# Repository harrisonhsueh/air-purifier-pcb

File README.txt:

using tnis plugin to generate bom for jlpcb assembly
https://github.com/Bouni/kicad-jlcpcb-tools

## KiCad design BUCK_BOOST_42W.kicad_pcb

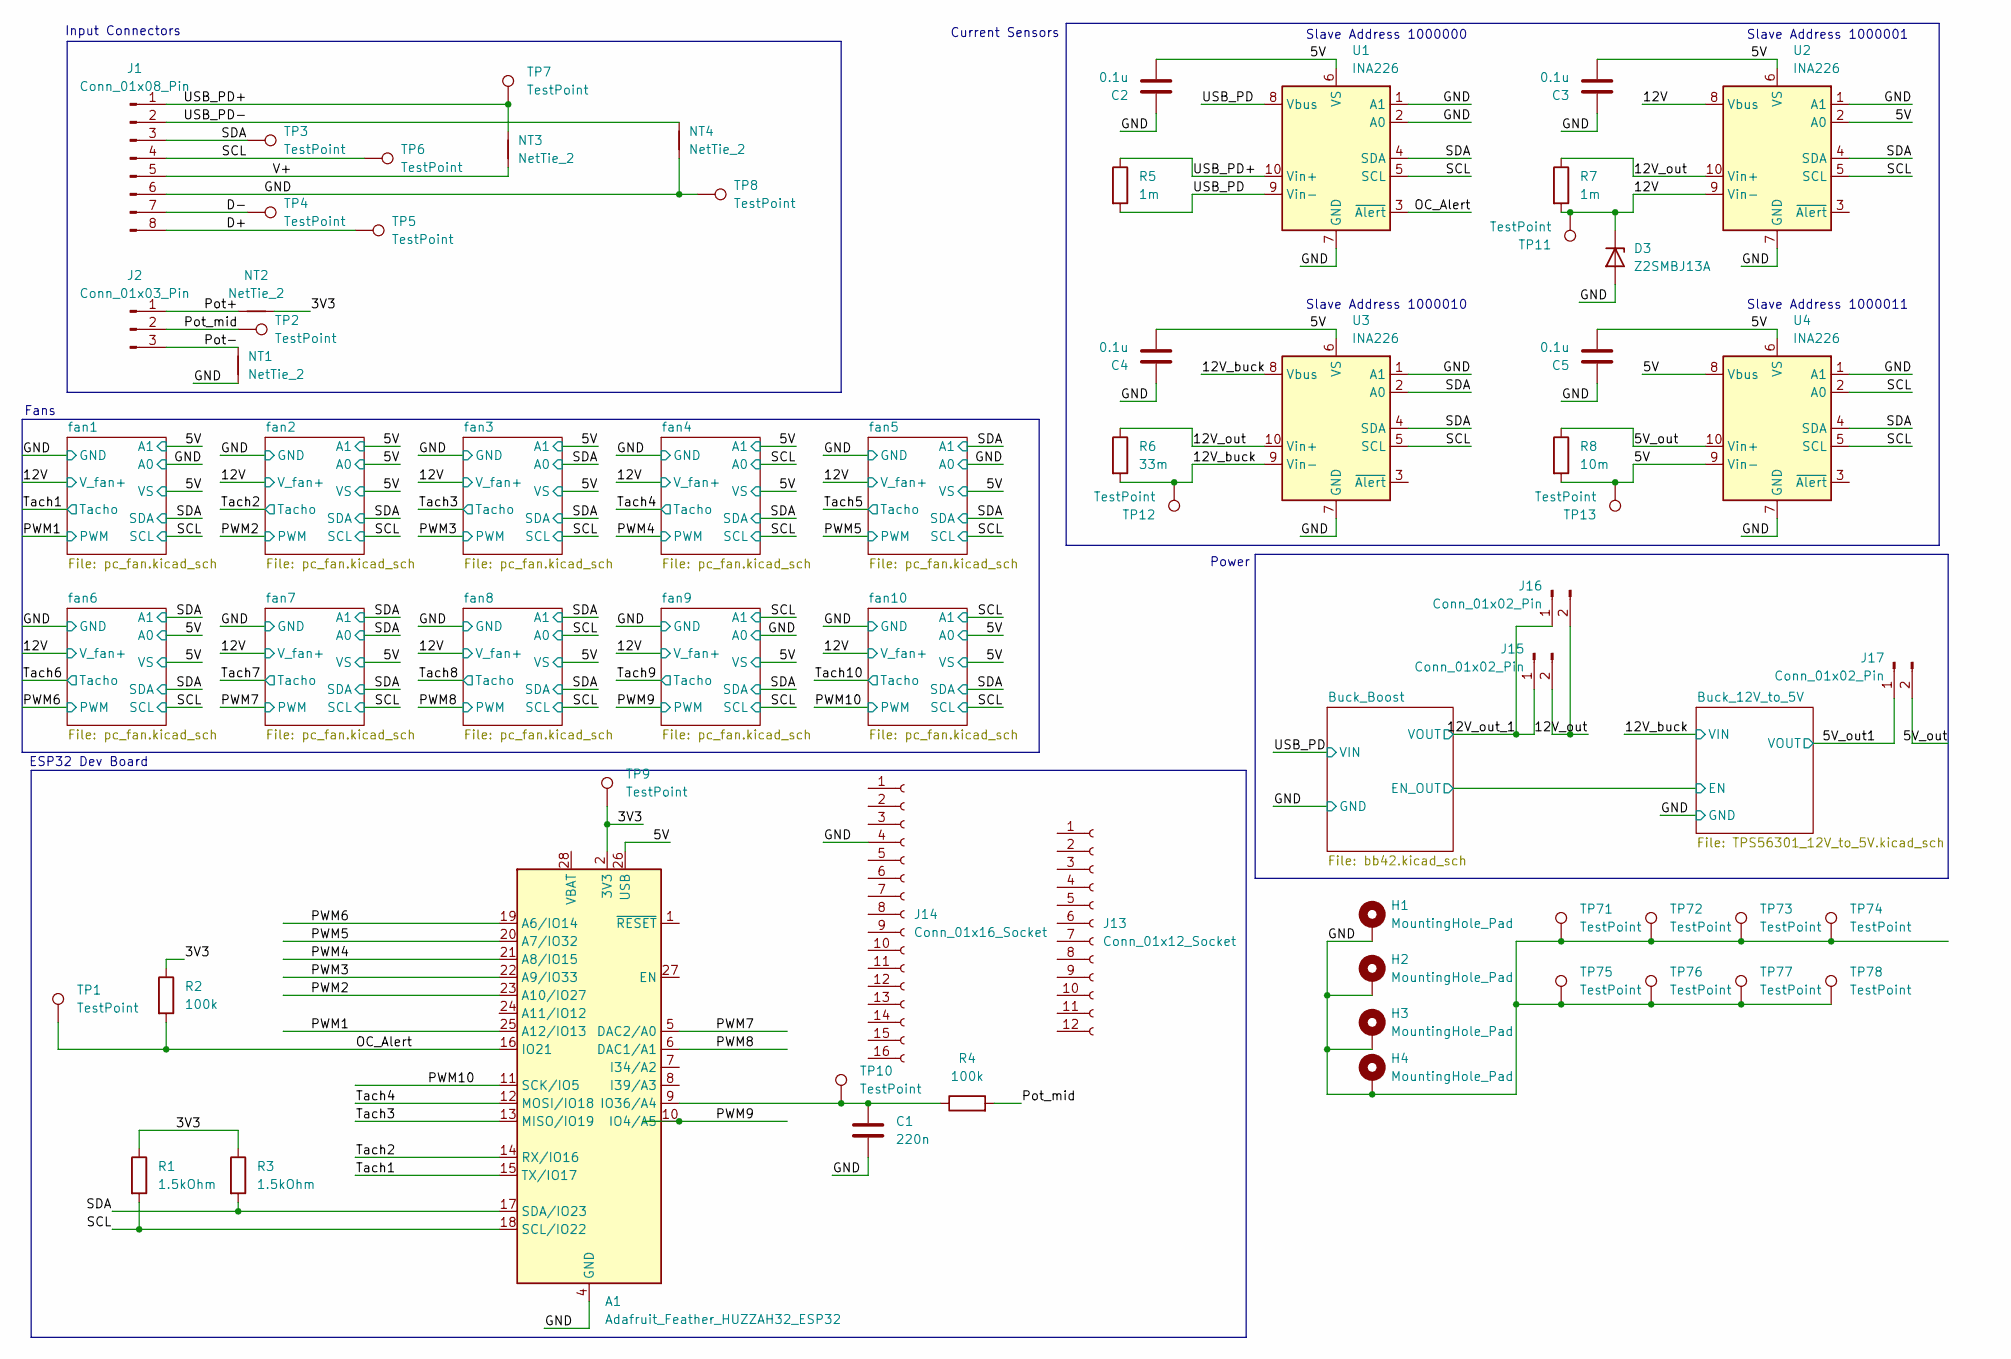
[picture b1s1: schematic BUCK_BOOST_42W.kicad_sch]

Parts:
A1: Adafruit_Feather_HUZZAH32_ESP32; Adafruit_Feather
C1: 220n; C_0603_1608Metric
C2: 0.1u; C_0603_1608Metric; Voltage 10
C3, C4, C5: 0.1u; C_0603_1608Metric
D3: Z2SMBJ13A; D_SMB
H1, H2, H3, H4: MountingHole_Pad; MountingHole_3.2mm_M3_DIN965_Pad
J1: Conn_01x08_Pin; JST_XH_B8B-XH-A_1x08_P2.50mm_Vertical
J2: Conn_01x03_Pin; JST_XH_B3B-XH-A_1x03_P2.50mm_Vertical
J13: Conn_01x12_Socket; PinSocket_1x12_P2.54mm_Vertical
J14: Conn_01x16_Socket; PinSocket_1x16_P2.54mm_Vertical
J15, J16, J17: Conn_01x02_Pin; PinHeader_1x02_P2.54mm_Vertical
NT1, NT2: NetTie_2; NetTie-2_SMD_Pad0.5mm
NT3, NT4: NetTie_2; NetTie-2_SMD_Pad2.0mm
R1, R3: 1.5kOhm; R_0603_1608Metric
R2, R4: 100k; R_0603_1608Metric
R5, R7: 1m; R_0612_1632Metric
R6: 33m; R_0603_1608Metric
R8: 10m; R_0805_2012Metric
TP1, TP2, TP3, TP4, TP5, TP6, TP7, TP8, TP9, TP10: TestPoint; TestPoint_Pad_D1.0mm
TP11, TP12, TP13: TestPoint; TestPoint_Plated_Hole_D2.0mm
TP71, TP72, TP73, TP74, TP75, TP76, TP77, TP78: TestPoint; TestPoint_Keystone_5000-5004_Miniature
U1, U2, U3, U4: INA226; VSSOP-10_3x3mm_P0.5mm

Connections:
/3V3: A1.2 (3V3), NT2.2, R1.1, R2.1, R3.1, TP9.1
/5V: A1.26 (USB), C2.2, C3.2, C4.2, C5.2, R8.2, TP13.1, U1.6 (VS), U2.2 (A0), U2.6 (VS), U3.6 (VS), U4.6 (VS), U4.8 (Vbus), U4.9 (Vin-); also elsewhere on the board
/5V_out: J17.2, R8.1, U4.10 (Vin+)
/5V_out1: J17.1; also elsewhere on the board
/12V: D3.1 (K), R7.2, TP11.1, U2.8 (Vbus), U2.9 (Vin-); also elsewhere on the board
/12V_buck: R6.2, TP12.1, U3.8 (Vbus), U3.9 (Vin-); also elsewhere on the board
/12V_out: J15.2, J16.2, R6.1, R7.1, U2.10 (Vin+), U3.10 (Vin+)
/12V_out_1: J15.1, J16.1; also elsewhere on the board
/D+: J1.8, TP5.1
/D-: J1.7, TP4.1
/GND: A1.4 (GND), C1.2, C2.1, C3.1, C4.1, C5.1, D3.2 (A), H1.1, H2.1, H3.1, H4.1, J1.6, J14.4, NT1.1, NT4.1, TP8.1, TP71.1, TP72.1, TP73.1, TP74.1, TP75.1, TP76.1, TP77.1, TP78.1, U1.1 (A1), U1.2 (A0), U1.7 (GND), U2.1 (A1), U2.7 (GND), U3.1 (A1), U3.7 (GND), U4.1 (A1), U4.7 (GND); also elsewhere on the board
/OC_Alert: A1.16 (IO21), R2.2, TP1.1, U1.3 (~Alert)
/PWM1: A1.25 (A12/IO13); also elsewhere on the board
/PWM2: A1.23 (A10/IO27); also elsewhere on the board
/PWM3: A1.22 (A9/IO33); also elsewhere on the board
/PWM4: A1.21 (A8/IO15); also elsewhere on the board
/PWM5: A1.20 (A7/IO32); also elsewhere on the board
/PWM6: A1.19 (A6/IO14); also elsewhere on the board
/PWM7: A1.5 (DAC2/A0); also elsewhere on the board
/PWM8: A1.6 (DAC1/A1); also elsewhere on the board
/PWM9: A1.10 (IO4/A5); also elsewhere on the board
/PWM10: A1.11 (SCK/IO5); also elsewhere on the board
/Pot+: J2.1, NT2.1
/Pot-: J2.3, NT1.2
/Pot_mid: J2.2, R4.2, TP2.1
/SCL: A1.18 (SCL/IO22), J1.4, R1.2, TP6.1, U1.5 (SCL), U2.5 (SCL), U3.5 (SCL), U4.2 (A0), U4.5 (SCL); also elsewhere on the board
/SDA: A1.17 (SDA/IO23), J1.3, R3.2, TP3.1, U1.4 (SDA), U2.4 (SDA), U3.2 (A0), U3.4 (SDA), U4.4 (SDA); also elsewhere on the board
/Tach1: A1.15 (TX/IO17); also elsewhere on the board
/Tach2: A1.14 (RX/IO16); also elsewhere on the board
/Tach3: A1.13 (MISO/IO19); also elsewhere on the board
/Tach4: A1.12 (MOSI/IO18); also elsewhere on the board
/USB_PD: R5.2, U1.8 (Vbus), U1.9 (Vin-); also elsewhere on the board
/USB_PD+: J1.1, NT3.2, R5.1, TP7.1, U1.10 (Vin+)
/USB_PD-: J1.2, NT4.2
/V+: J1.5, NT3.1
unnamed: A1.9 (IO36/A4), C1.1, R4.1, TP10.1

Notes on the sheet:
Slave Address 1000000
Fans
ESP32 Dev Board
Power
Slave Address 1000010
Input Connectors
Slave Address 1000011
Current Sensors
Slave Address 1000001

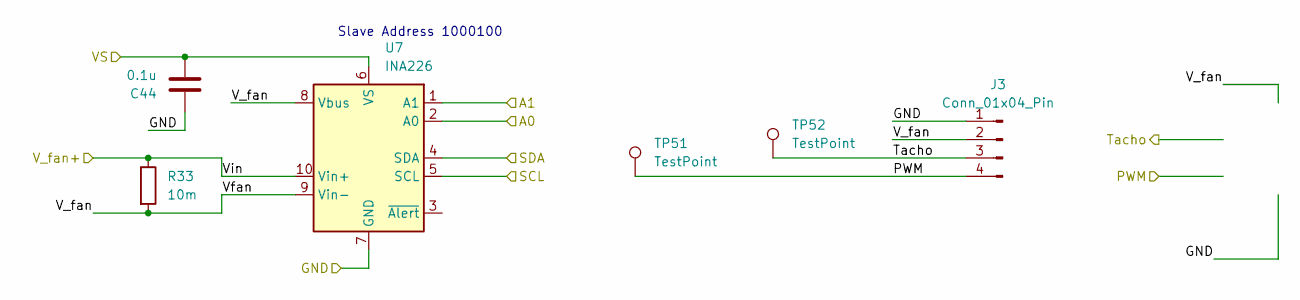
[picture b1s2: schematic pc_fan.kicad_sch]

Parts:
C44: 0.1u; C_0603_1608Metric
J3: Conn_01x04_Pin; FanPinHeader_1x04_P2.54mm_Vertical
R33: 10m; R_0805_2012Metric
TP51, TP52: TestPoint; TestPoint_Pad_D1.0mm
U7: INA226; VSSOP-10_3x3mm_P0.5mm

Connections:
/5V: C44.2, U7.1 (A1), U7.6 (VS); also elsewhere on the board
/12V: R33.1, U7.10 (Vin+); also elsewhere on the board
/GND: C44.1, J3.1, U7.2 (A0), U7.7 (GND); also elsewhere on the board
/PWM1: J3.4, TP51.1; also elsewhere on the board
/SCL: U7.5 (SCL); also elsewhere on the board
/SDA: U7.4 (SDA); also elsewhere on the board
/Tach1: J3.3, TP52.1; also elsewhere on the board
/fan1/V_fan: J3.2, R33.2, U7.8 (Vbus), U7.9 (Vin-)

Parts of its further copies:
C45, C46, C47, C48, C49, C50, C51, C52, C53: 0.1u; C_0603_1608Metric
J4, J5, J6, J7, J8, J9, J10, J11, J12: Conn_01x04_Pin; FanPinHeader_1x04_P2.54mm_Vertical
R34, R35, R36, R37, R38, R39, R40, R41, R42: 10m; R_0805_2012Metric
TP53, TP54, TP55, TP56, TP57, TP58, TP59, TP60, TP61, TP62, TP63, TP64, TP65, TP66, TP67, TP68, TP69, TP70: TestPoint; TestPoint_Pad_D1.0mm
U8, U9, U10, U11, U12, U13, U14, U15, U16: INA226; VSSOP-10_3x3mm_P0.5mm

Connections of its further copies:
/5V: C45.2, C46.2, C47.2, C48.2, C49.2, C50.2, C51.2, C52.2, C53.2, U8.1 (A1), U8.2 (A0), U8.6 (VS), U9.1 (A1), U9.6 (VS), U10.1 (A1), U10.6 (VS), U11.6 (VS), U12.2 (A0), U12.6 (VS), U13.6 (VS), U14.6 (VS), U15.6 (VS), U16.2 (A0), U16.6 (VS); also elsewhere on the board
/12V: R34.1, R35.1, R36.1, R37.1, R38.1, R39.1, R40.1, R41.1, R42.1, U8.10 (Vin+), U9.10 (Vin+), U10.10 (Vin+), U11.10 (Vin+), U12.10 (Vin+), U13.10 (Vin+), U14.10 (Vin+), U15.10 (Vin+), U16.10 (Vin+); also elsewhere on the board
/GND: C45.1, C46.1, C47.1, C48.1, C49.1, C50.1, C51.1, C52.1, C53.1, J4.1, J5.1, J6.1, J7.1, J8.1, J9.1, J10.1, J11.1, J12.1, U8.7 (GND), U9.7 (GND), U10.7 (GND), U11.2 (A0), U11.7 (GND), U12.7 (GND), U13.7 (GND), U14.7 (GND), U15.2 (A0), U15.7 (GND), U16.7 (GND); also elsewhere on the board
/PWM2: J4.4, TP53.1; also elsewhere on the board
/PWM3: J5.4, TP55.1; also elsewhere on the board
/PWM4: J6.4, TP57.1; also elsewhere on the board
/PWM5: J7.4, TP59.1; also elsewhere on the board
/PWM6: J8.4, TP61.1; also elsewhere on the board
/PWM7: J9.4, TP63.1; also elsewhere on the board
/PWM8: J10.4, TP65.1; also elsewhere on the board
/PWM9: J11.4, TP67.1; also elsewhere on the board
/PWM10: J12.4, TP69.1; also elsewhere on the board
/SCL: U8.5 (SCL), U9.5 (SCL), U10.2 (A0), U10.5 (SCL), U11.5 (SCL), U12.5 (SCL), U13.5 (SCL), U14.2 (A0), U14.5 (SCL), U15.1 (A1), U15.5 (SCL), U16.1 (A1), U16.5 (SCL); also elsewhere on the board
/SDA: U8.4 (SDA), U9.2 (A0), U9.4 (SDA), U10.4 (SDA), U11.1 (A1), U11.4 (SDA), U12.1 (A1), U12.4 (SDA), U13.1 (A1), U13.2 (A0), U13.4 (SDA), U14.1 (A1), U14.4 (SDA), U15.4 (SDA), U16.4 (SDA); also elsewhere on the board
/Tach2: J4.3, TP54.1; also elsewhere on the board
/Tach3: J5.3, TP56.1; also elsewhere on the board
/Tach4: J6.3, TP58.1; also elsewhere on the board
/Tach5: J7.3, TP60.1
/Tach6: J8.3, TP62.1
/Tach7: J9.3, TP64.1
/Tach8: J10.3, TP66.1
/Tach9: J11.3, TP68.1
/Tach10: J12.3, TP70.1
/fan2/V_fan: J4.2, R34.2, U8.8 (Vbus), U8.9 (Vin-)
/fan3/V_fan: J5.2, R35.2, U9.8 (Vbus), U9.9 (Vin-)
/fan4/V_fan: J6.2, R36.2, U10.8 (Vbus), U10.9 (Vin-)
/fan5/V_fan: J7.2, R37.2, U11.8 (Vbus), U11.9 (Vin-)
/fan6/V_fan: J8.2, R38.2, U12.8 (Vbus), U12.9 (Vin-)
/fan7/V_fan: J9.2, R39.2, U13.8 (Vbus), U13.9 (Vin-)
/fan8/V_fan: J10.2, R40.2, U14.8 (Vbus), U14.9 (Vin-)
/fan9/V_fan: J11.2, R41.2, U15.8 (Vbus), U15.9 (Vin-)
/fan10/V_fan: J12.2, R42.2, U16.8 (Vbus), U16.9 (Vin-)

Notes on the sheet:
Slave Address 1000100

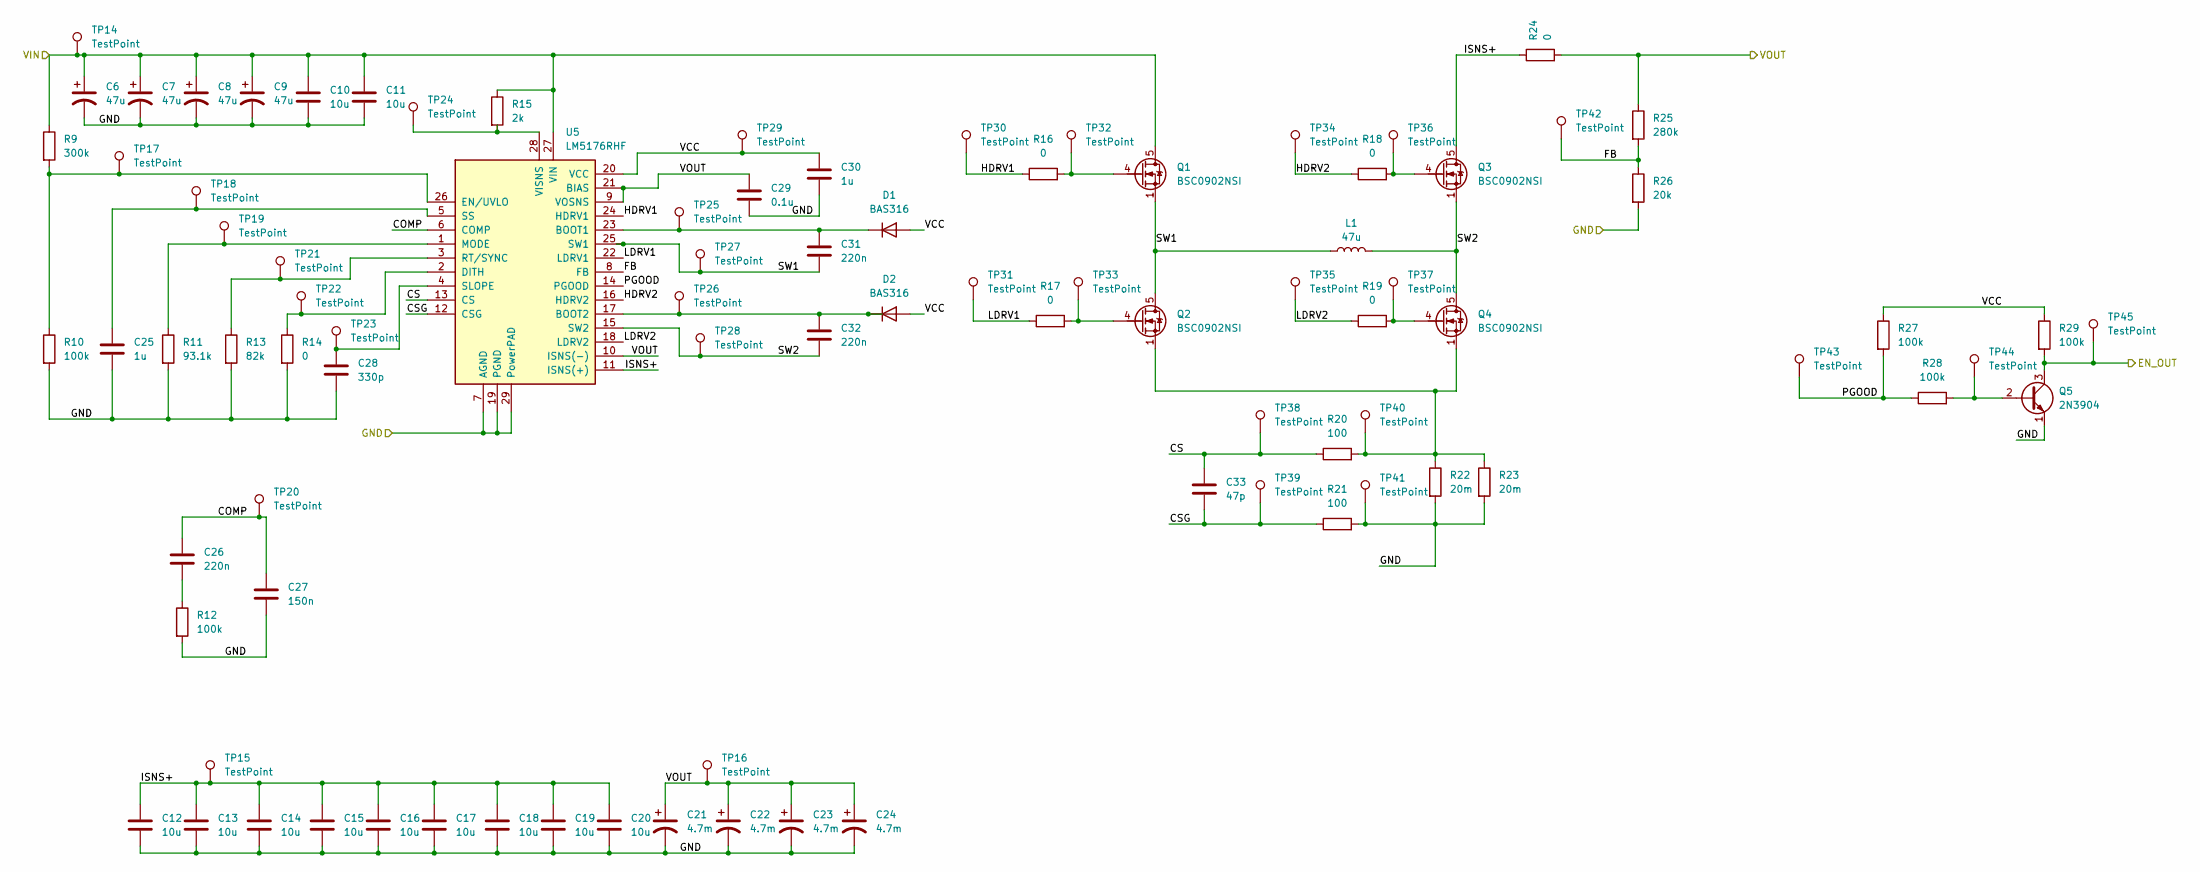
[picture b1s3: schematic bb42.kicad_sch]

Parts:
C6, C7, C8, C9: 47u; CP_Radial_D5.0mm_P2.00mm
C10, C11, C12, C13, C14, C15, C16, C17, C18, C19, C20: 10u; C_1206_3216Metric
C21, C22, C23, C24: 4.7m; CP_Radial_D18.0mm_P7.50mm
C25, C30: 1u; C_0603_1608Metric
C26, C31, C32: 220n; C_0603_1608Metric
C27: 150n; C_0603_1608Metric
C28: 330p; C_0603_1608Metric
C29: 0.1u; C_0603_1608Metric
C33: 47p; C_0603_1608Metric
D1, D2: BAS316; D_SOD-323
L1: 47u; L_Wuerth_HCF-2013
Q1, Q2, Q3, Q4: BSC0902NSI; TDSON-8-1
Q5: 2N3904; TSOT-23
R9: 300k; R_0603_1608Metric
R10, R12, R27, R28, R29: 100k; R_0603_1608Metric
R11: 93.1k; R_0603_1608Metric
R13: 82k; R_0603_1608Metric
R14, R16, R17, R18, R19: 0; R_0603_1608Metric
R15: 2k; R_0603_1608Metric
R20, R21: 100; R_0603_1608Metric
R22, R23: 20m; R_0612_1632Metric
R24: 0; R_0612_1632Metric
R25: 280k; R_0603_1608Metric
R26: 20k; R_0603_1608Metric
TP14, TP15, TP16, TP17, TP18, TP19, TP20, TP21, TP22, TP23, TP24, TP25, TP26, TP27, TP28, TP29, TP30, TP31, TP32, TP33, TP34, TP35, TP36, TP37, TP38, TP39, TP40, TP41, TP42, TP43, TP44, TP45: TestPoint; TestPoint_Pad_D1.0mm
U5: LM5176RHF; VQFN-28-1EP_4x5mm_P0.5mm_EP2.55x3.55mm

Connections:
/12V_out_1: C21.1, C22.1, C23.1, C24.1, C29.1, R24.2, R25.1, TP16.1, U5.9 (VOSNS), U5.10 (ISNS(-)), U5.21 (BIAS); also elsewhere on the board
/Buck_12V_to_5V/EN: Q5.3 (C), R29.2, TP45.1; also elsewhere on the board
/Buck_Boost/COMP: C26.1, C27.1, TP20.1, U5.6 (COMP)
/Buck_Boost/CS: C33.1, R20.1, TP38.1, U5.13 (CS)
/Buck_Boost/CSG: C33.2, R21.1, TP39.1, U5.12 (CSG)
/Buck_Boost/FB: R25.2, R26.1, TP42.1, U5.8 (FB)
/Buck_Boost/HDRV1: R16.1, TP30.1, U5.24 (HDRV1)
/Buck_Boost/HDRV2: R18.1, TP34.1, U5.16 (HDRV2)
/Buck_Boost/ISNS+: C12.1, C13.1, C14.1, C15.1, C16.1, C17.1, C18.1, C19.1, C20.1, Q3.5 (D), R24.1, TP15.1, U5.11 (ISNS(+))
/Buck_Boost/LDRV1: R17.1, TP31.1, U5.22 (LDRV1)
/Buck_Boost/LDRV2: R19.1, TP35.1, U5.18 (LDRV2)
/Buck_Boost/PGOOD: R27.2, R28.1, TP43.1, U5.14 (PGOOD)
/Buck_Boost/SW1: C31.2, L1.1, Q1.1 (S), Q1.2 (S), Q1.3 (S), Q2.5 (D), TP27.1, U5.25 (SW1)
/Buck_Boost/SW2: C32.2, L1.2, Q3.1 (S), Q3.2 (S), Q3.3 (S), Q4.5 (D), TP28.1, U5.15 (SW2)
/Buck_Boost/VCC: C30.1, D1.2 (A), D2.2 (A), R27.1, R29.1, TP29.1, U5.20 (VCC)
/GND: C6.2, C7.2, C8.2, C9.2, C10.2, C11.2, C12.2, C13.2, C14.2, C15.2, C16.2, C17.2, C18.2, C19.2, C20.2, C21.2, C22.2, C23.2, C24.2, C25.2, C27.2, C28.2, C29.2, C30.2, Q5.1 (E), R10.2, R11.2, R12.2, R13.2, R14.2, R21.2, R22.2, R23.2, R26.2, TP41.1, U5.7 (AGND), U5.19 (PGND), U5.29 (PowerPAD); also elsewhere on the board
/USB_PD: C6.1, C7.1, C8.1, C9.1, C10.1, C11.1, Q1.5 (D), R9.1, R15.1, TP14.1, U5.27 (VIN); also elsewhere on the board
unnamed: C26.2, R12.1
unnamed: C31.1, D1.1 (K), TP25.1, U5.23 (BOOT1)
unnamed: C32.1, D2.1 (K), TP26.1, U5.17 (BOOT2)
unnamed: Q1.4 (G), R16.2, TP32.1
unnamed: Q2.4 (G), R17.2, TP33.1
unnamed: Q2.1 (S), Q2.2 (S), Q2.3 (S), Q4.1 (S), Q4.2 (S), Q4.3 (S), R20.2, R22.1, R23.1, TP40.1
unnamed: Q3.4 (G), R18.2, TP36.1
unnamed: Q4.4 (G), R19.2, TP37.1
unnamed: Q5.2 (B), R28.2, TP44.1
unnamed: R14.1, TP22.1, U5.2 (DITH)
unnamed: R9.2, R10.1, TP17.1, U5.26 (EN/UVLO)
unnamed: R11.1, TP19.1, U5.1 (MODE)
unnamed: R13.1, TP21.1, U5.3 (RT/SYNC)
unnamed: C28.1, TP23.1, U5.4 (SLOPE)
unnamed: C25.1, TP18.1, U5.5 (SS)
unnamed: R15.2, TP24.1, U5.28 (VISNS)

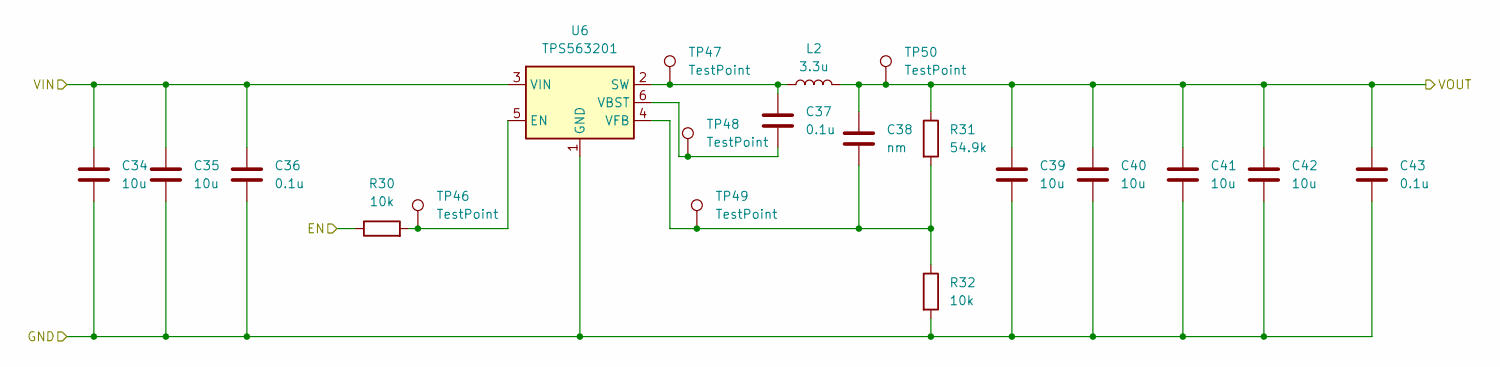
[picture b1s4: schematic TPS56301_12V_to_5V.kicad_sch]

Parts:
C34, C35, C39, C40, C41, C42: 10u; C_1206_3216Metric
C36, C37, C43: 0.1u; C_0603_1608Metric
C38: nm; C_0603_1608Metric
L2: 3.3u; L_TDK_VLS6045EX_VLS6045AF
R30, R32: 10k; R_0603_1608Metric
R31: 54.9k; R_0603_1608Metric
TP46, TP47, TP48, TP49, TP50: TestPoint; TestPoint_Pad_D1.0mm
U6: TPS563201; SOT-23-6

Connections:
/5V_out1: C38.1, C39.1, C40.1, C41.1, C42.1, C43.1, L2.2, R31.1, TP50.1; also elsewhere on the board
/12V_buck: C34.1, C35.1, C36.1, U6.3 (VIN); also elsewhere on the board
/Buck_12V_to_5V/EN: R30.1; also elsewhere on the board
/GND: C34.2, C35.2, C36.2, C39.2, C40.2, C41.2, C42.2, C43.2, R32.2, U6.1 (GND); also elsewhere on the board
unnamed: R30.2, TP46.1, U6.5 (EN)
unnamed: C37.1, L2.1, TP47.1, U6.2 (SW)
unnamed: C37.2, TP48.1, U6.6 (VBST)
unnamed: C38.2, R31.2, R32.1, TP49.1, U6.4 (VFB)

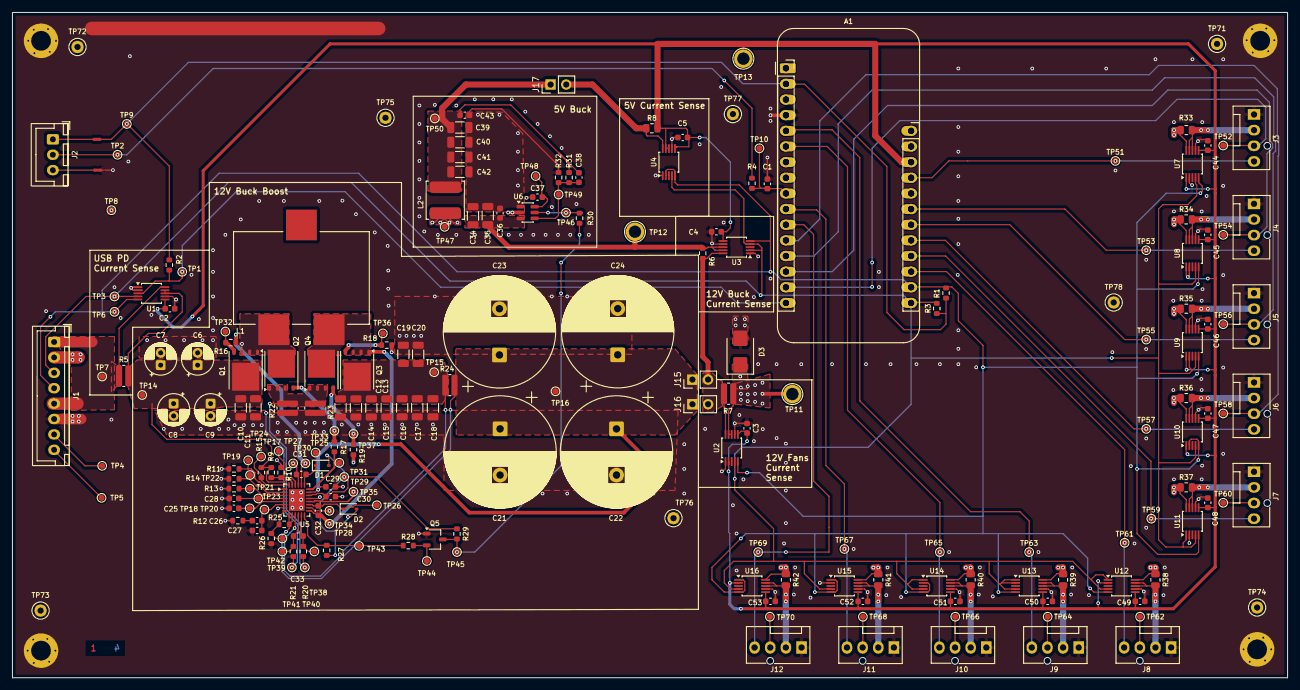
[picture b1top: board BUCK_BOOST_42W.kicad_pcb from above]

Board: 4 copper layers, 207.0 x 108.0 mm, 225 parts (0 on the bottom side), 86 nets.

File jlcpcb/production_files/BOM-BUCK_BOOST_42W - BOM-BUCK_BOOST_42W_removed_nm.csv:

Comment,Designator,Footprint,LCSC,Quantity
220n,"C1,C26,C31,C32",C_0603_1608Metric,C21120,4
10u,"C10,C11,C12,C13,C14,C15,C16,C17,C18,C19,C20,C34,C35,C39,C40,C41,C42",C_1206_3216Metric,C13585,17
0.1u,"C2,C29,C3,C36,C37,C4,C43,C44,C45,C46,C47,C48,C49,C5,C50,C51,C52,C53",C_0603_1608Metric,C14663,18
4.7m,"C21,C22,C23,C24",CP_Radial_D18.0mm_P7.50mm,C442850,4
1u,"C25,C30",C_0603_1608Metric,C15849,2
150n,C27,C_0603_1608Metric,C513735,1
330p,C28,C_0603_1608Metric,C1664,1
47p,C33,C_0603_1608Metric,C1671,1
47u,"C6,C7,C8",CP_Radial_D5.0mm_P2.00mm,C724770,3
47u,C9,CP_Radial_D5.0mm_P2.00mm,C432384,1
BAS316,"D1,D2",D_SOD-323,C109218,2
Z2SMBJ13A,D3,D_SMB,C5161161,1
Conn_01x08_Pin,J1,JST_XH_B8B-XH-A_1x08_P2.50mm_Vertical,C157972,1
Conn_01x04_Pin,"J10,J11,J12,J3,J4,J5,J6,J7,J8,J9",FanPinHeader_1x04_P2.54mm_Vertical,C240840,10
Conn_01x12_Socket,J13,PinSocket_1x12_P2.54mm_Vertical,C2905419,1
Conn_01x16_Socket,J14,PinSocket_1x16_P2.54mm_Vertical,C2905421,1
Conn_01x03_Pin,J2,JST_XH_B3B-XH-A_1x03_P2.50mm_Vertical,C51940188,1
47u,L1,L_Wuerth_HCF-2013,C2651192,1
3.3u,L2,L_TDK_VLS6045EX_VLS6045AF,C307879,1
BSC098N10NS5,"Q1,Q2,Q3,Q4",Infineon_PG-TDSON-8_6.15x5.15mm,C534398,4
2N3904,Q5,TSOT-23,C81464,1
1.5kOhm,"R1,R3",R_0603_1608Metric,C22843,2
100k,"R10,R12,R2,R27,R28,R29,R4",R_0603_1608Metric,C25803,7
93.1k,R11,R_0603_1608Metric,C228101,1
82k,R13,R_0603_1608Metric,C23254,1
0,"R14,R16,R17,R18,R19",R_0603_1608Metric,C21189,5
2k,R15,R_0603_1608Metric,C22975,1
100,"R20,R21",R_0603_1608Metric,C22775,2
20m,"R22,R23",R_0612_1632Metric,C713438,2
0,R24,R_0612_1632Metric,C2074805,1
280k,R25,R_0603_1608Metric,C22970,1
20k,R26,R_0603_1608Metric,C4184,1
10k,"R30,R32",R_0603_1608Metric,C25804,2
54.9k,R31,R_0603_1608Metric,C23077,1
10m,"R33,R34,R35,R36,R37,R38,R39,R40,R41,R42,R8",R_0805_2012Metric,C728271,11
1m,"R5,R7",R_0612_1632Metric,C21261111,2
33m,R6,R_0603_1608Metric,C859741,1
300k,R9,R_0603_1608Metric,C23024,1
TestPoint,"TP71,TP72,TP73,TP74,TP75,TP76,TP77,TP78",TestPoint_Keystone_5000-5004_Miniature,C5199801,8
INA226,"U1,U10,U11,U12,U13,U14,U15,U16,U2,U3,U4,U7,U8,U9",VSSOP-10_3x3mm_P0.5mm,C49851,14
LM5176RHF,U5,VQFN-28-1EP_4x5mm_P0.5mm_EP2.55x3.55mm,C1850330,1
TPS563201,U6,SOT-23-6,C116592,1

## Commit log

2026-04-10 Version 1 design being manufactured
2026-04-28 sense resistor partial changes
2026-04-28 format and pdf of schematic
2026-04-28 layout pdf files
2026-05-08 organized pdf locations
2026-05-08 rework made on v1 1st pcb for comp and ss
2026-05-08 removed diode net yet implemented and pdf of layout page bb
